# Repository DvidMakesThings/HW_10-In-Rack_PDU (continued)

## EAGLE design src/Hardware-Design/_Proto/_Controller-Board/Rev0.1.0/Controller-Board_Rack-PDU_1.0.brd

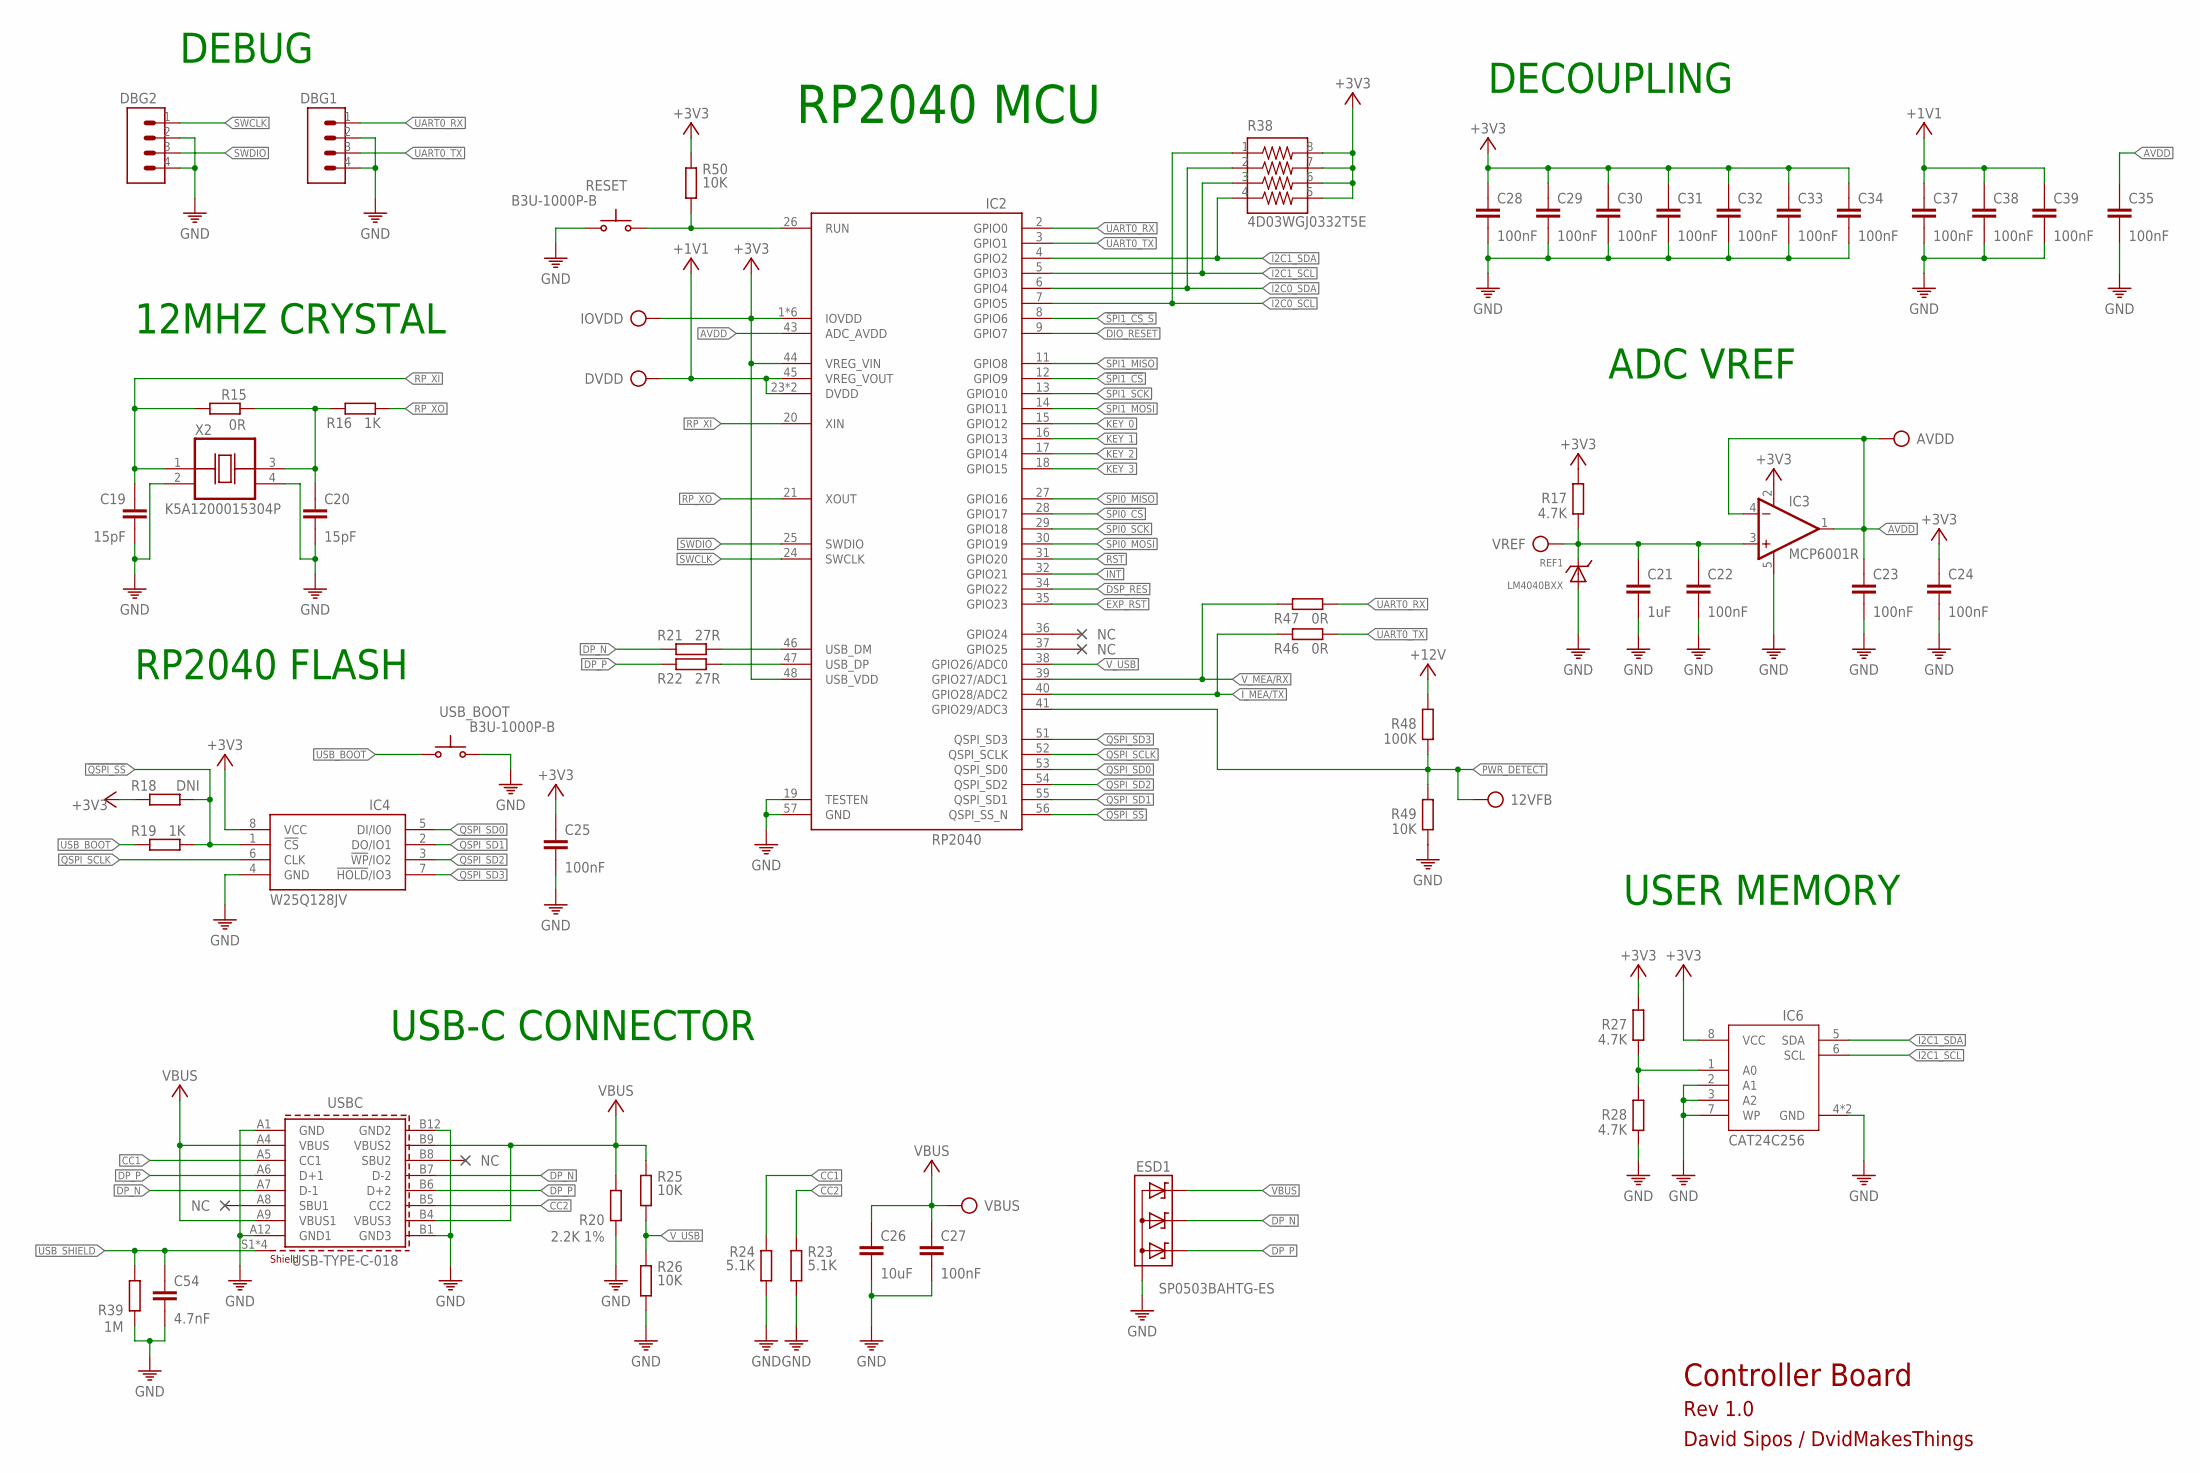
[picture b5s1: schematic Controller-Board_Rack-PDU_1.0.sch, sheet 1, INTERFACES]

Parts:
12VFB: TP
AVDD: TP
C19, C20: 15pF; C0402
C21: 1uF; C0402
C22, C23, C24, C25, C28, C29, C30, C31, C32, C33, C34, C35, C37, C38, C39: 100nF; C0402
C26: 10uF; 0805
C27: 100nF; 0402
C54: 4.7nF; 0402
DBG1, DBG2: CON-1X4; 1X4
DVDD: TP
ESD1: SP0503BAHTG-ES; SOT143
IC2: RP2040; QFN40P700X700X100-57T510
IC3: MCP6001R; SOT23-5
IC4: W25Q128JVPIQ; SON127P600X500X75-8N
IC6: CAT24C256HU4IGT3; SON50P300X200X50-9T130X140N
IOVDD: TP
R15, R46, R47: 0R; 0402
R16, R19: 1K; 0402
R17, R27, R28: 4.7K; 0402
R18: DNI; 0402
R20: 2.2K 1%; 0402
R21, R22: 27R; 0402
R23, R24: 5.1K; 0402
R25, R26, R49, R50: 10K; 0402
R38: 4D03WGJ0332T5E; 742C083103JP
R39: 1M; 0402
R48: 100K; 0402
REF1: LM4040BXX; SOT23
RESET: B3U-1000P-B; SWITCH-OMRON_B3U-1000P
USBC: USB-TYPE-C-018; 629722000214
USB_BOOT: B3U-1000P-B; SWITCH-OMRON_B3U-1000P
VBUS: TP
VREF: TP
X2: K5A1200015304P; OSCCC500X320X130

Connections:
!INT: IC2.32 (GPIO21); also elsewhere on the board
!QSPI_SS: IC2.56 (QSPI_SS_N), IC4.1 (!CS), R18.1, R19.2
!RST: IC2.31 (GPIO20); also elsewhere on the board
!SPI0_CS: IC2.28 (GPIO17); also elsewhere on the board
!SPI1_CS: IC2.12 (GPIO9); also elsewhere on the board
!SPI1_CS_S: IC2.8 (GPIO6); also elsewhere on the board
+1V1: C37.1, C38.1, C39.1, DVDD.TP, IC2.23 (DVDD), IC2.45 (VREG_VOUT), IC2.50 (DVDD)
+3V3: C24.1, C25.1, C28.1, C29.1, C30.1, C31.1, C32.1, C33.1, C34.1, IC2.1 (IOVDD), IC2.10 (IOVDD), IC2.22 (IOVDD), IC2.33 (IOVDD), IC2.42 (IOVDD), IC2.44 (VREG_VIN), IC2.48 (USB_VDD), IC2.49 (IOVDD), IC3.2 (V+), IC4.8 (VCC), IC6.8 (VCC), IOVDD.TP, R17.2, R18.2, R27.2, R38.5, R38.6, R38.7, R38.8, R50.1; also elsewhere on the board
+12V: R48.2; also elsewhere on the board
AVDD: AVDD.TP, C23.1, C35.1, IC2.43 (ADC_AVDD), IC3.1 (OUT), IC3.4 (-IN)
CC1: R24.1, USBC.A5 (CC1)
CC2: R23.1, USBC.B5 (CC2)
DIO_RESET: IC2.9 (GPIO7); also elsewhere on the board
DP_N: ESD1.3 (C2), R21.1, USBC.A7 (D-1), USBC.B7 (D-2)
DP_P: ESD1.2 (C1), R22.1, USBC.A6 (D+1), USBC.B6 (D+2)
DSP_RES: IC2.34 (GPIO22); also elsewhere on the board
EXP_RST: IC2.35 (GPIO23); also elsewhere on the board
GND: C19.2, C20.2, C21.2, C22.2, C23.2, C24.2, C25.2, C26.2, C27.2, C28.2, C29.2, C30.2, C31.2, C32.2, C33.2, C34.2, C35.2, C37.2, C38.2, C39.2, C54.2, DBG1.2, DBG1.4, DBG2.2, DBG2.4, ESD1.1 (A), IC2.19 (TESTEN), IC2.57 (GND), IC3.5 (V-), IC4.4 (GND), IC6.2 (A1), IC6.3 (A2), IC6.4 (GND), IC6.7 (WP), IC6.9 (GND), R20.2, R23.2, R24.2, R26.2, R28.1, R39.2, R49.1, REF1.2 (A), REF1.3 (A), RESET.2 (S), USBC.A1 (GND), USBC.A12 (GND1), USBC.B1 (GND3), USBC.B12 (GND2), USB_BOOT.2 (S), X2.2 (VSS), X2.4 (VDD); also elsewhere on the board
I2C0_SCL: IC2.7 (GPIO5), R38.1; also elsewhere on the board
I2C0_SDA: IC2.6 (GPIO4), R38.2; also elsewhere on the board
I2C1_SCL: IC2.5 (GPIO3), IC6.6 (SCL), R38.3
I2C1_SDA: IC2.4 (GPIO2), IC6.5 (SDA), R38.4
I_MEA/TX: IC2.40 (GPIO28/ADC2), R46.1; also elsewhere on the board
KEY_0: IC2.15 (GPIO12); also elsewhere on the board
KEY_1: IC2.16 (GPIO13); also elsewhere on the board
KEY_2: IC2.17 (GPIO14); also elsewhere on the board
KEY_3: IC2.18 (GPIO15); also elsewhere on the board
unnamed: C20.1, R15.2, R16.1, X2.3 (OUT)
unnamed: IC2.26 (RUN), R50.2, RESET.1
unnamed: IC6.1 (A0), R27.1, R28.2
PWR_DETECT: 12VFB.TP, IC2.41 (GPIO29/ADC3), R48.1, R49.2
QSPI_SCLK: IC2.52 (QSPI_SCLK), IC4.6 (CLK)
QSPI_SD0: IC2.53 (QSPI_SD0), IC4.5 (DI/IO0)
QSPI_SD1: IC2.55 (QSPI_SD1), IC4.2 (DO/IO1)
QSPI_SD2: IC2.54 (QSPI_SD2), IC4.3 (!WP!/IO2)
QSPI_SD3: IC2.51 (QSPI_SD3), IC4.7 (!HOLD!/IO3)
RP_XI: C19.1, IC2.20 (XIN), R15.1, X2.1 (CON)
RP_XO: IC2.21 (XOUT), R16.2
SPI0_MISO: IC2.27 (GPIO16); also elsewhere on the board
SPI0_MOSI: IC2.30 (GPIO19); also elsewhere on the board
SPI0_SCK: IC2.29 (GPIO18); also elsewhere on the board
SPI1_MISO: IC2.11 (GPIO8); also elsewhere on the board
SPI1_MOSI: IC2.14 (GPIO11); also elsewhere on the board
SPI1_SCK: IC2.13 (GPIO10); also elsewhere on the board
SWCLK: DBG2.1, IC2.24 (SWCLK)
SWDIO: DBG2.3, IC2.25 (SWDIO)
UART0_RX: DBG1.1, IC2.2 (GPIO0), R47.2
UART0_TX: DBG1.3, IC2.3 (GPIO1), R46.2
USB_BOOT: R19.1, USB_BOOT.1
USB_DP_N: IC2.46 (USB_DM), R21.2
USB_DP_P: IC2.47 (USB_DP), R22.2
USB_SHIELD: C54.1, R39.1, USBC.S1 (SHIELD), USBC.S2 (SHIELD), USBC.S3 (SHIELD), USBC.S4 (SHIELD)
VBUS: C26.1, C27.1, ESD1.4 (C3), R20.1, R25.1, USBC.A4 (VBUS), USBC.A9 (VBUS1), USBC.B4 (VBUS3), USBC.B9 (VBUS2), VBUS.TP
VREF: C21.1, C22.1, IC3.3 (+IN), R17.1, REF1.1 (C), VREF.TP
V_MEA/RX: IC2.39 (GPIO27/ADC1), R47.1; also elsewhere on the board
V_USB: IC2.38 (GPIO26/ADC0), R25.2, R26.1

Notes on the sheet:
USB-C CONNECTOR
DECOUPLING
12MHZ CRYSTAL
RP2040 MCU
RP2040 FLASH
USER MEMORY
ADC VREF
DEBUG
Controller Board
Rev 1.0
David Sipos / DvidMakesThings

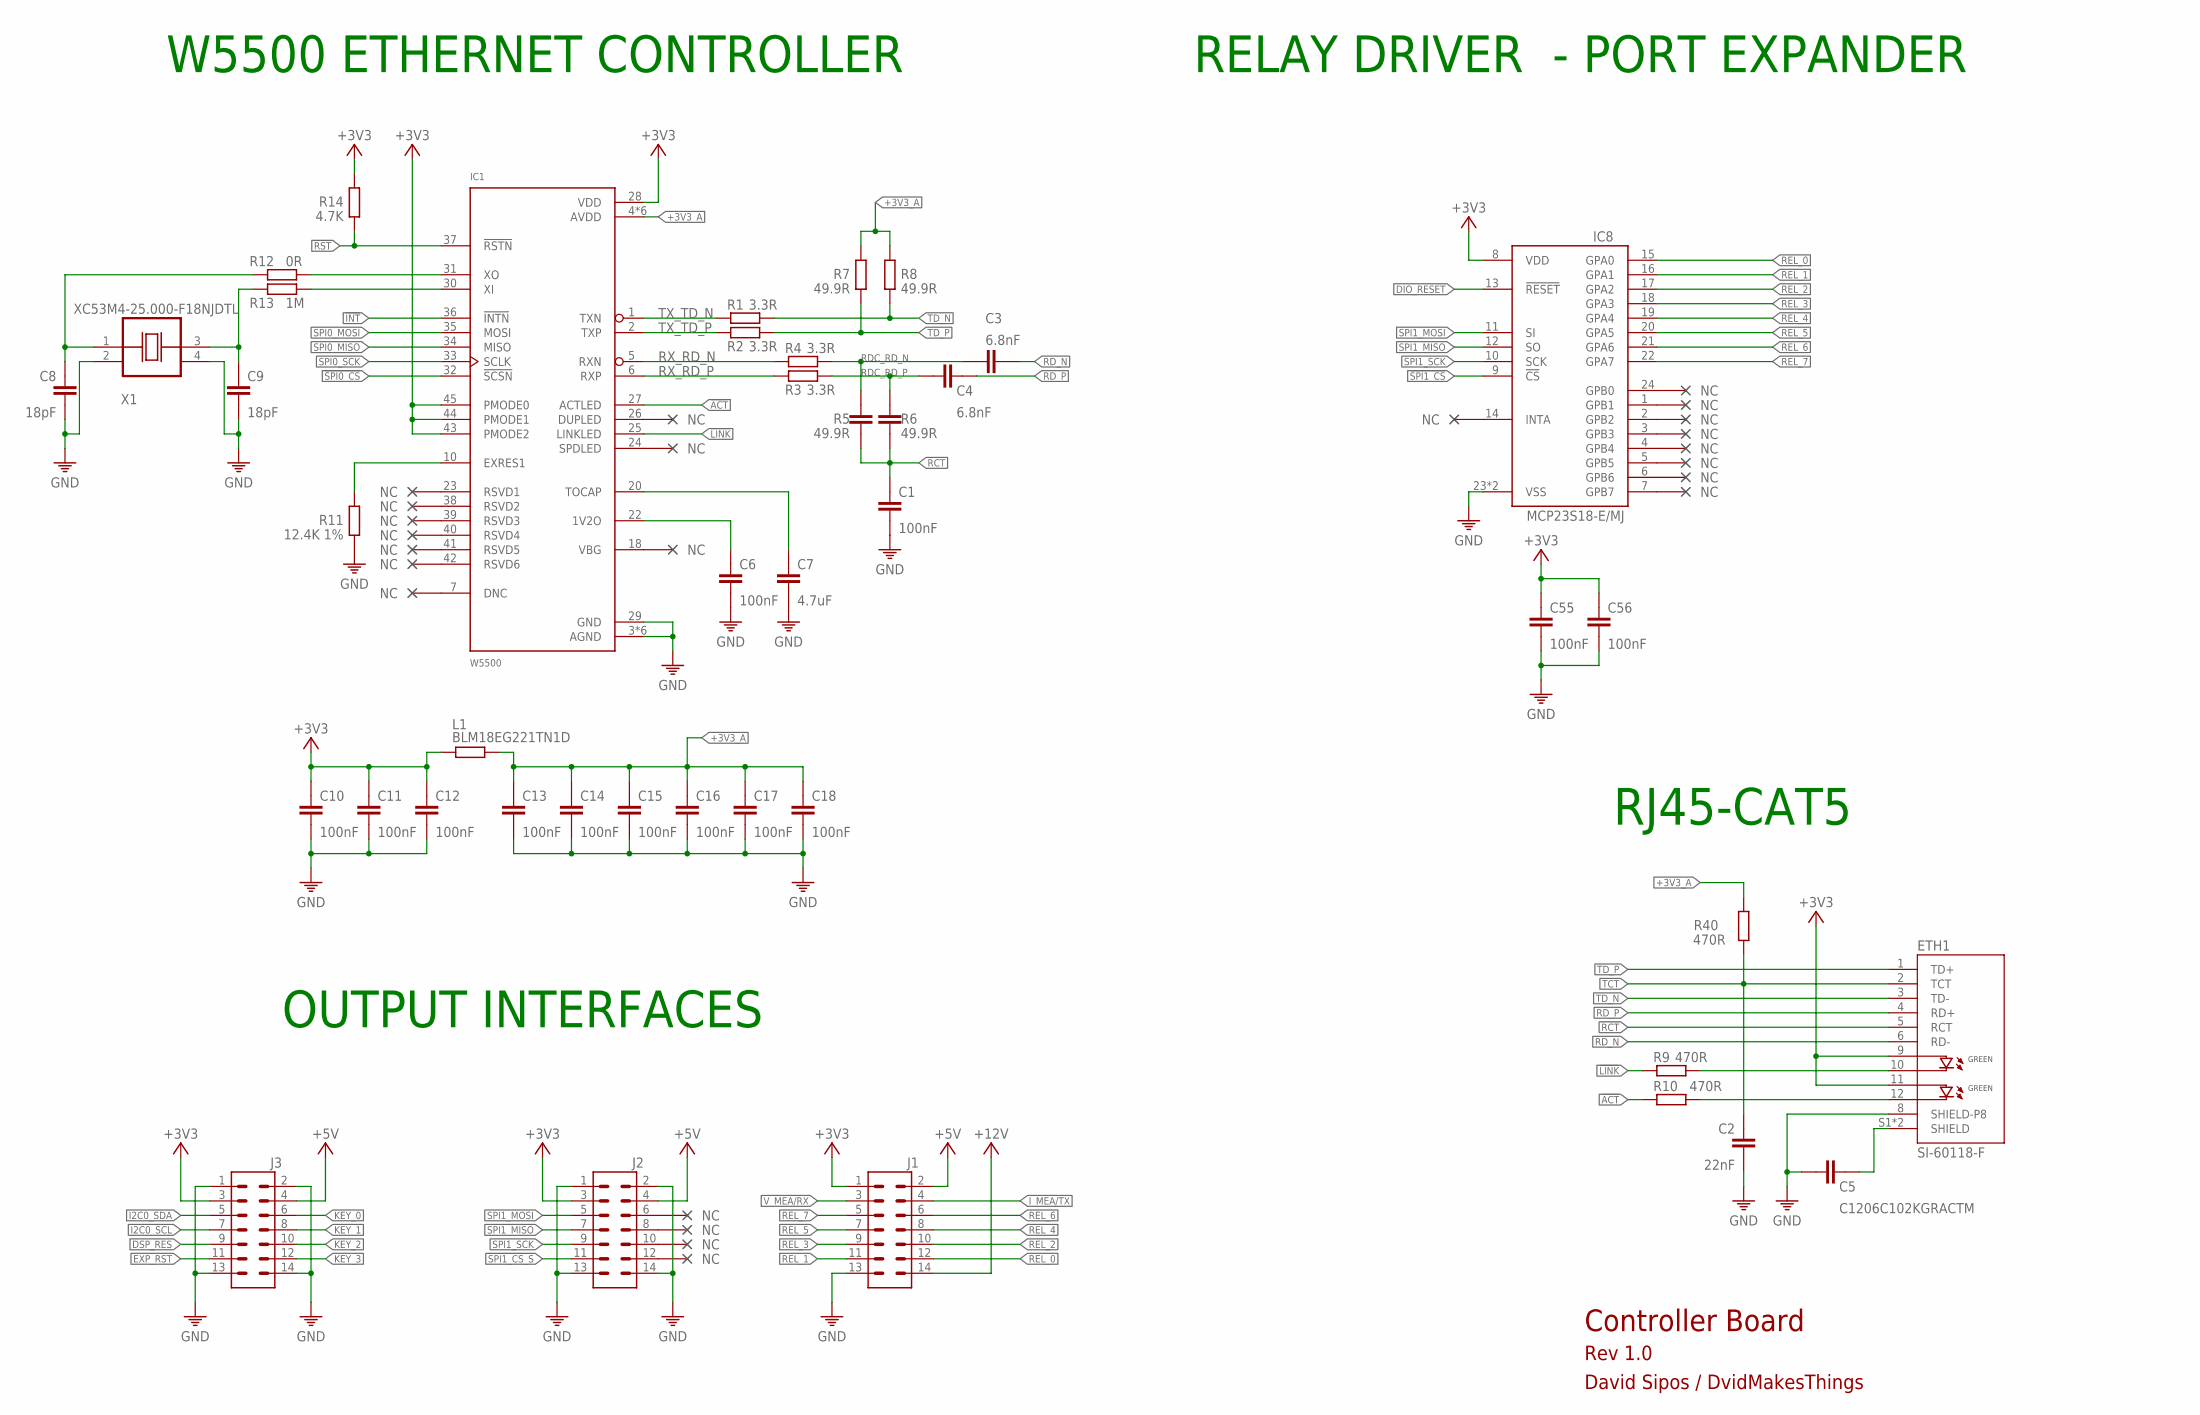
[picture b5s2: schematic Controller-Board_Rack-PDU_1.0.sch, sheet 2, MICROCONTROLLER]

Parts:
C1, C6, C10, C11, C12, C13, C14, C15, C16, C17, C18, C55, C56: 100nF; C0402
C2: 22nF; C0402
C3, C4: 6.8nF; C0402
C5: C1206C102KGRACTM; C1206
C7: 4.7uF; C0402
C8, C9: 18pF; C0402
ETH1: SI-60118-F; RJ45-CAT5
IC1: W5500; LQFP48
IC8: MCP23S18-E/MJ; QFN50P400X400X100-25T265
J1, J2, J3: CON-2X7; 2X7
L1: BLM18EG221TN1D; 0603
R1, R2, R3, R4: 3.3R; 0402
R5, R6: 49.9R; C0402
R7, R8: 49.9R; 0402
R9, R10, R40: 470R; 0402
R11: 12.4K 1%; 0402
R12: 0R; 0402
R13: 1M; 0402
R14: 4.7K; 0402
X1: XC53M4-25.000-F18NJDTL; OSCCC500X320X130

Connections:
!ACT: IC1.27 (ACTLED), R10.1
!INT: IC1.36 (!INTN); also elsewhere on the board
!LINK: IC1.25 (LINKLED), R9.1
!RST: IC1.37 (!RSTN), R14.1; also elsewhere on the board
!SPI0_CS: IC1.32 (!SCSN); also elsewhere on the board
!SPI1_CS: IC8.9 (!CS); also elsewhere on the board
!SPI1_CS_S: J2.11; also elsewhere on the board
+3V3: C10.1, C11.1, C12.1, C55.1, C56.1, ETH1.9 (GA1), ETH1.11 (GA2), IC1.28 (VDD), IC1.43 (PMODE2), IC1.44 (PMODE1), IC1.45 (PMODE0), IC8.8 (VDD), J1.1, J2.3, J3.3, L1.1, R14.2; also elsewhere on the board
+3V3_A: C13.1, C14.1, C15.1, C16.1, C17.1, C18.1, IC1.4 (AVDD), IC1.8 (AVDD), IC1.11 (AVDD), IC1.15 (AVDD), IC1.17 (AVDD), IC1.21 (AVDD), L1.2, R7.2, R8.2, R40.2
+5V: J1.2, J2.4, J3.4; also elsewhere on the board
+12V: J1.14; also elsewhere on the board
CHASSIS: C5.2, ETH1.S1 (SHIELD), ETH1.S2 (SHIELD)
DIO_RESET: IC8.13 (!RESET); also elsewhere on the board
DSP_RES: J3.9; also elsewhere on the board
EXP_RST: J3.11; also elsewhere on the board
GND: C1.2, C2.2, C5.1, C6.2, C7.2, C8.2, C9.2, C10.2, C11.2, C12.2, C13.2, C14.2, C15.2, C16.2, C17.2, C18.2, C55.2, C56.2, ETH1.8 (SHIELD-P8), IC1.3 (AGND), IC1.9 (AGND), IC1.14 (AGND), IC1.16 (AGND), IC1.19 (AGND), IC1.29 (GND), IC1.48 (AGND), IC8.23 (VSS), IC8.25 (VSS), J1.13, J2.1, J2.2, J2.13, J2.14, J3.1, J3.2, J3.13, J3.14, R11.1, X1.2 (VSS), X1.4 (VDD); also elsewhere on the board
I2C0_SCL: J3.7; also elsewhere on the board
I2C0_SDA: J3.5; also elsewhere on the board
I_MEA/TX: J1.4; also elsewhere on the board
KEY_0: J3.6; also elsewhere on the board
KEY_1: J3.8; also elsewhere on the board
KEY_2: J3.10; also elsewhere on the board
KEY_3: J3.12; also elsewhere on the board
unnamed: IC1.10 (EXRES1), R11.2
unnamed: ETH1.10 (GK1), R9.2
unnamed: ETH1.12 (GK2), R10.2
unnamed: C6.1, IC1.22 (1V2O)
unnamed: C7.1, IC1.20 (TOCAP)
unnamed: C8.1, R12.1, X1.1 (CON)
unnamed: C9.1, R13.1, X1.3 (OUT)
unnamed: IC1.31 (XO), R12.2
unnamed: IC1.30 (XI), R13.2
RCT: C1.1, ETH1.5 (RCT), R5.1, R6.1
RDC_RD_N: C3.1, R4.2, R5.2
RDC_RD_P: C4.1, R3.2, R6.2
RD_N: C3.2, ETH1.6 (RD-)
RD_P: C4.2, ETH1.4 (RD+)
REL_0: IC8.15 (GPA0), J1.12
REL_1: IC8.16 (GPA1), J1.11
REL_2: IC8.17 (GPA2), J1.10
REL_3: IC8.18 (GPA3), J1.9
REL_4: IC8.19 (GPA4), J1.8
REL_5: IC8.20 (GPA5), J1.7
REL_6: IC8.21 (GPA6), J1.6
REL_7: IC8.22 (GPA7), J1.5
RX_RD_N: IC1.5 (RXN), R4.1
RX_RD_P: IC1.6 (RXP), R3.1
SPI0_MISO: IC1.34 (MISO); also elsewhere on the board
SPI0_MOSI: IC1.35 (MOSI); also elsewhere on the board
SPI0_SCK: IC1.33 (SCLK); also elsewhere on the board
SPI1_MISO: IC8.12 (SO), J2.7; also elsewhere on the board
SPI1_MOSI: IC8.11 (SI), J2.5; also elsewhere on the board
SPI1_SCK: IC8.10 (SCK), J2.9; also elsewhere on the board
TCT: C2.1, ETH1.2 (TCT), R40.1
TD_N: ETH1.3 (TD-), R1.2, R8.1
TD_P: ETH1.1 (TD+), R2.2, R7.1
TX_TD_N: IC1.1 (TXN), R1.1
TX_TD_P: IC1.2 (TXP), R2.1
V_MEA/RX: J1.3; also elsewhere on the board

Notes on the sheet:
W5500 ETHERNET CONTROLLER
RJ45-CAT5
OUTPUT INTERFACES
RELAY DRIVER - PORT EXPANDER
Controller Board
Rev 1.0
David Sipos / DvidMakesThings

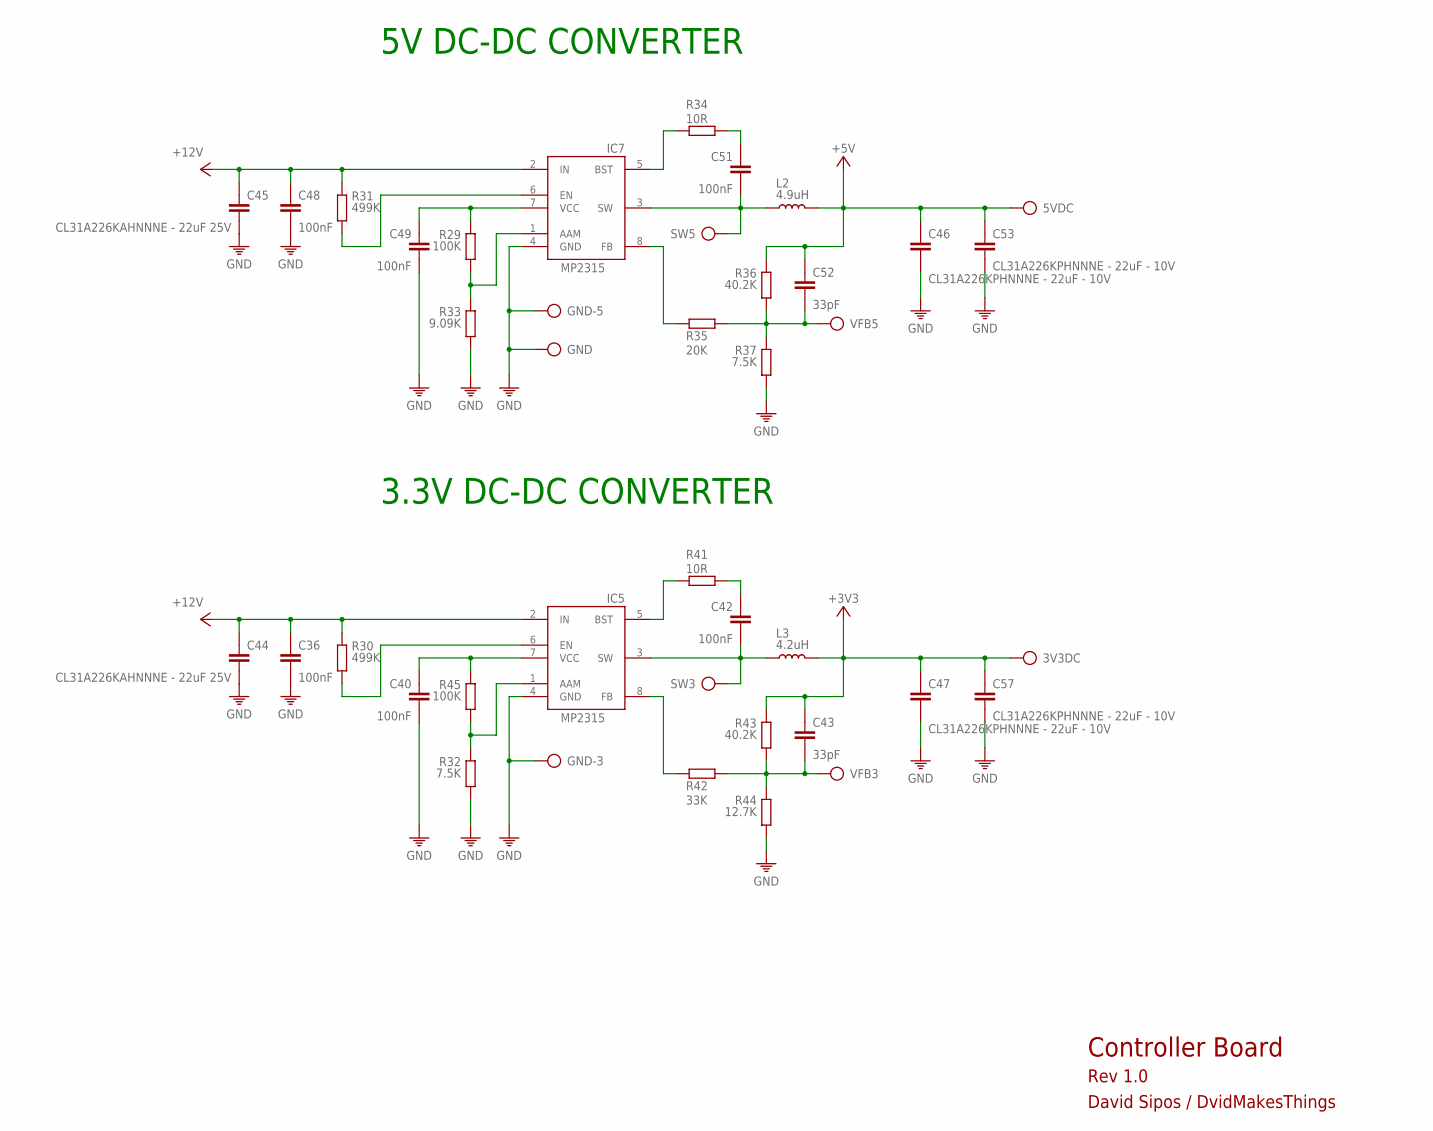
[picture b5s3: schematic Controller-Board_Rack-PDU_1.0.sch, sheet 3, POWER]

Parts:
3V3DC, 5VDC: TP
C36, C40, C42, C48, C49, C51: 100nF; 0402
C43, C52: 33pF; 0402
C44, C45: CL31A226KAHNNNE - 22uF 25V; C1206
C46, C47, C53, C57: CL31A226KPHNNNE - 22uF - 10V; C1206
GND: TP
GND-3, GND-5: TP
IC5: MP2315S; SOT65P280X110-8N
IC7: MP2315GJ-Z; SOT65P280X110-8N
L2: 4.9uH; SRR5228A
L3: 4.2uH; SRR5228A
R29, R45: 100K; 0402
R30, R31: 499K; 0402
R32, R37: 7.5K; 0402
R33: 9.09K; 0402
R34, R41: 10R; 0402
R35: 20K; 0402
R36, R43: 40.2K; 0402
R42: 33K; 0402
R44: 12.7K; 0402
SW3, SW5: TP
VFB3, VFB5: TP

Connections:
+3V3: 3V3DC.TP, C43.1, C47.1, C57.1, L3.2, R43.1; also elsewhere on the board
+5V: 5VDC.TP, C46.1, C52.1, C53.1, L2.2, R36.1; also elsewhere on the board
+12V: C36.1, C44.1, C45.1, C48.1, IC5.2 (IN), IC7.2 (IN), R30.1, R31.1; also elsewhere on the board
GND: C36.2, C40.2, C44.2, C45.2, C46.2, C47.2, C48.2, C49.2, C53.2, C57.2, GND.TP, GND-3.TP, GND-5.TP, IC5.4 (GND), IC7.4 (GND), R32.2, R33.2, R37.2, R44.2; also elsewhere on the board
unnamed: IC5.5 (BST), R41.2
unnamed: IC5.1 (AAM), R32.1, R45.2
unnamed: IC7.1 (AAM), R29.2, R33.1
unnamed: IC7.6 (EN), R31.2
unnamed: C49.1, IC7.7 (VCC), R29.1
unnamed: IC5.8 (FB), R42.1
unnamed: C42.2, IC5.3 (SW), L3.1, SW3.TP
unnamed: C42.1, R41.1
unnamed: C43.2, R42.2, R43.2, R44.1, VFB3.TP
unnamed: IC5.6 (EN), R30.2
unnamed: C40.1, IC5.7 (VCC), R45.1
unnamed: IC7.5 (BST), R34.2
unnamed: IC7.8 (FB), R35.1
unnamed: C51.2, IC7.3 (SW), L2.1, SW5.TP
unnamed: C51.1, R34.1
unnamed: C52.2, R35.2, R36.2, R37.1, VFB5.TP

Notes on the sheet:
5V DC-DC CONVERTER
Controller Board
Rev 1.0
David Sipos / DvidMakesThings
3.3V DC-DC CONVERTER

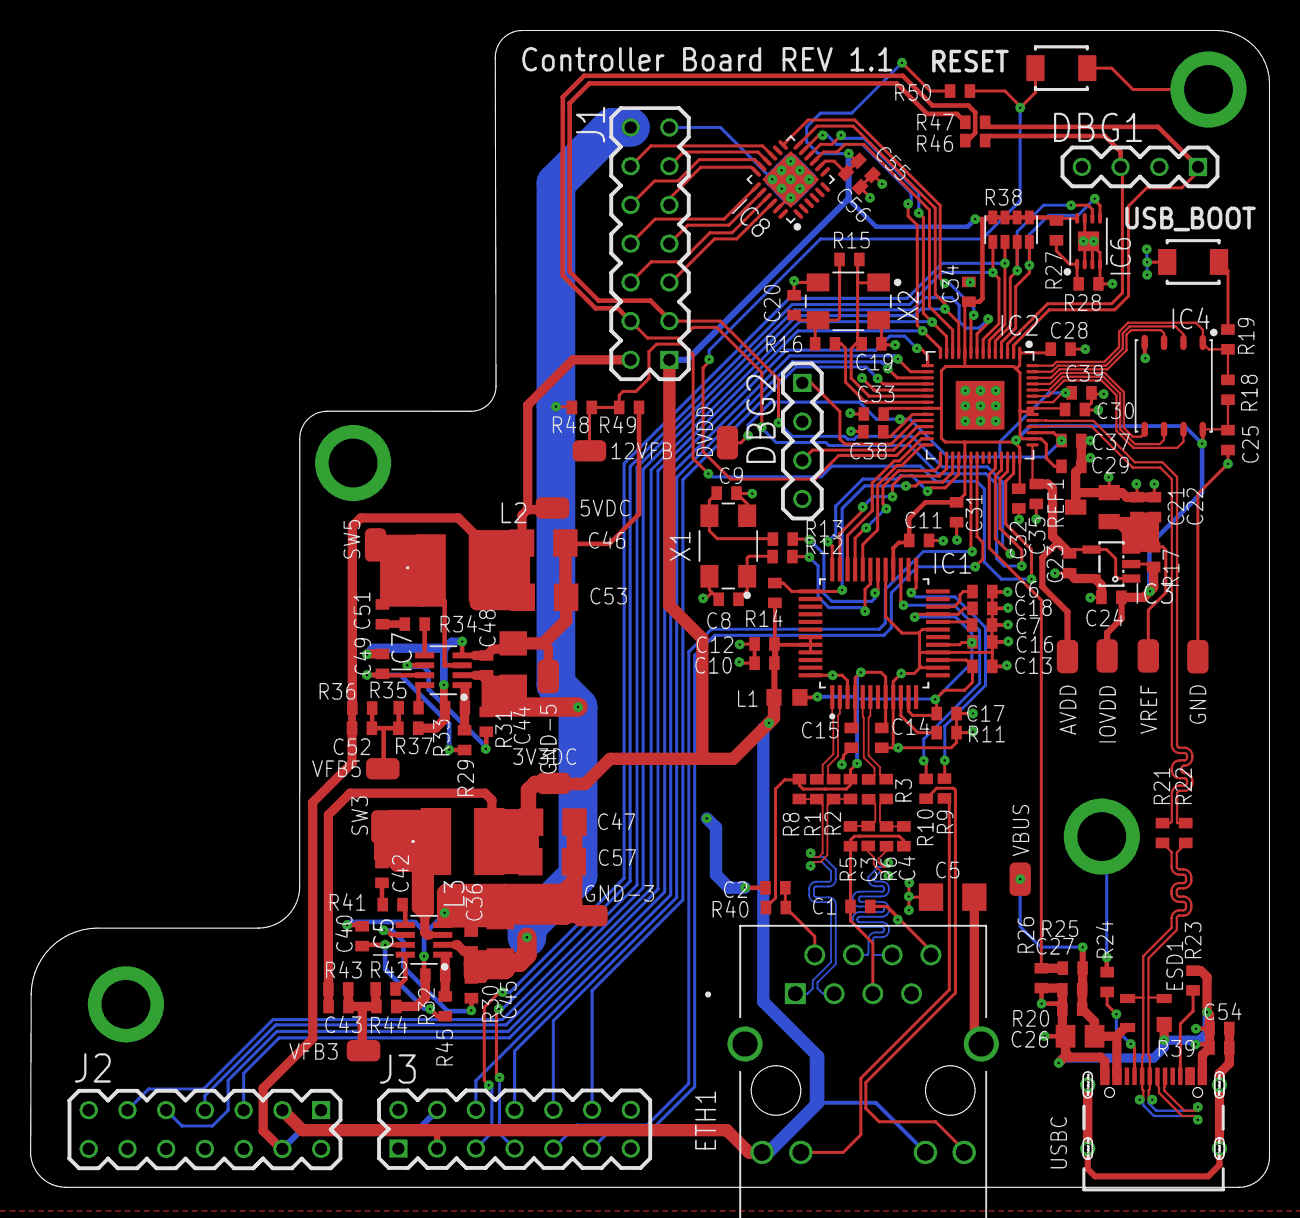
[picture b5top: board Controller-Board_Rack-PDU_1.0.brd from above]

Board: 4 copper layers, 81.3 x 75.9 mm, 144 parts (0 on the bottom side), 106 nets.

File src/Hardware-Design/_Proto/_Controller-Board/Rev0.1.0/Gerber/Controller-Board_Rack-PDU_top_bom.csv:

Comment,Designator,Footprint,LCSC Part #
0R,R12 R15 R46 R47,0402,
1K,R16 R19,0402,
1M,R13 R39,0402,
1uF,C21,C0402,
2.2K 1%,R20,0402,
3.3R,R1 R2 R3 R4,0402,
4.2uH,L3,SRR5228A,
4.7K,R14 R17 R27 R28 R48 R49,0402,
4.7nF,C54,0402,
4.7uF,C7,C0402,
4.9uH,L2,SRR5228A,
4D03WGJ0332T5E,R38,742C083103JP,
5.1K,R23 R24,0402,
5.6K,R25,0402,
6.8nF,C3 C4,C0402,
7.5K,R32 R37,0402,
9.09K,R33,0402,
10K,R26 R50,0402,
10R,R34 R41,0402,
10uF,C26,0805,
12.4K 1%,R11,0402,
12.7K,R44,0402,
15pF,C19 C20,C0402,
18pF,C8 C9,C0402,
20K,R35,0402,
22nF,C2,C0402,
27R,R21 R22,0402,
33K,R42,0402,
33pF,C43 C52,0402,
40.2K,R36 R43,0402,
49.9R,R5 R6,C0402,
49.9R,R7 R8,0402,
100K,R29 R45,0402,
100nF,C1 C6 C10 C11 C12 C13 C14 C15 C16 C17 C18 C22 C23 C24 C25,C0402,
100nF,C27,0402,
100nF,C28 C29 C30 C31 C32 C33 C34 C35,C0402,
100nF,C36,0402,
100nF,C37 C38 C39,C0402,
100nF,C40 C42 C48 C49 C51,0402,
100nF,C55 C56,C0402,
470R,R9 R10 R40,0402,
499K,R30 R31,0402,
B3U-1000P-B,RESET USB_BOOT,SWITCH-OMRON_B3U-1000P,
BLM18EG221TN1D,L1,0603,
C1206C102KGRACTM,C5,C1206,
CAT24C256WI-GT3,IC6,SON50P300X200X50-9T130X140N,
CL31A226KAHNNNE - 22uF 25V,C44 C45,C1206,
CL31A226KPHNNNE - 22uF - 10V,C46 C47 C53 C57,C1206,
DNI,R18,0402,
LM4040BXX,REF1,SOT23,
MCP23S18-E/MJ,IC8,QFN50P400X400X100-25T265,
MCP6001AIDBVRG,IC3,SOT23-5,
MP2315GJ-Z,IC7,SOT65P280X110-8N,
MP2315S ,IC5,SOT65P280X110-8N,
RL250001791,X1,OSCCC500X320X130,
RP2040,IC2,QFN40P700X700X100-57T510,
SP0503BAHTG-ES,ESD1,SOT143,
SX3M12.000B10F20TNN,X2,OSCCC500X320X130,
TP,3V3DC 5VDC 12VFB AVDD DVDD GND GND-3 GND-5 IOVDD SW3 SW5 VBUS VFB3 VFB5 VREF,TP,
USB-TYPE-C-018,USBC,629722000214,
W25Q128JVPIQ,IC4,SON127P600X500X75-8N,
W5500,IC1,LQFP48,

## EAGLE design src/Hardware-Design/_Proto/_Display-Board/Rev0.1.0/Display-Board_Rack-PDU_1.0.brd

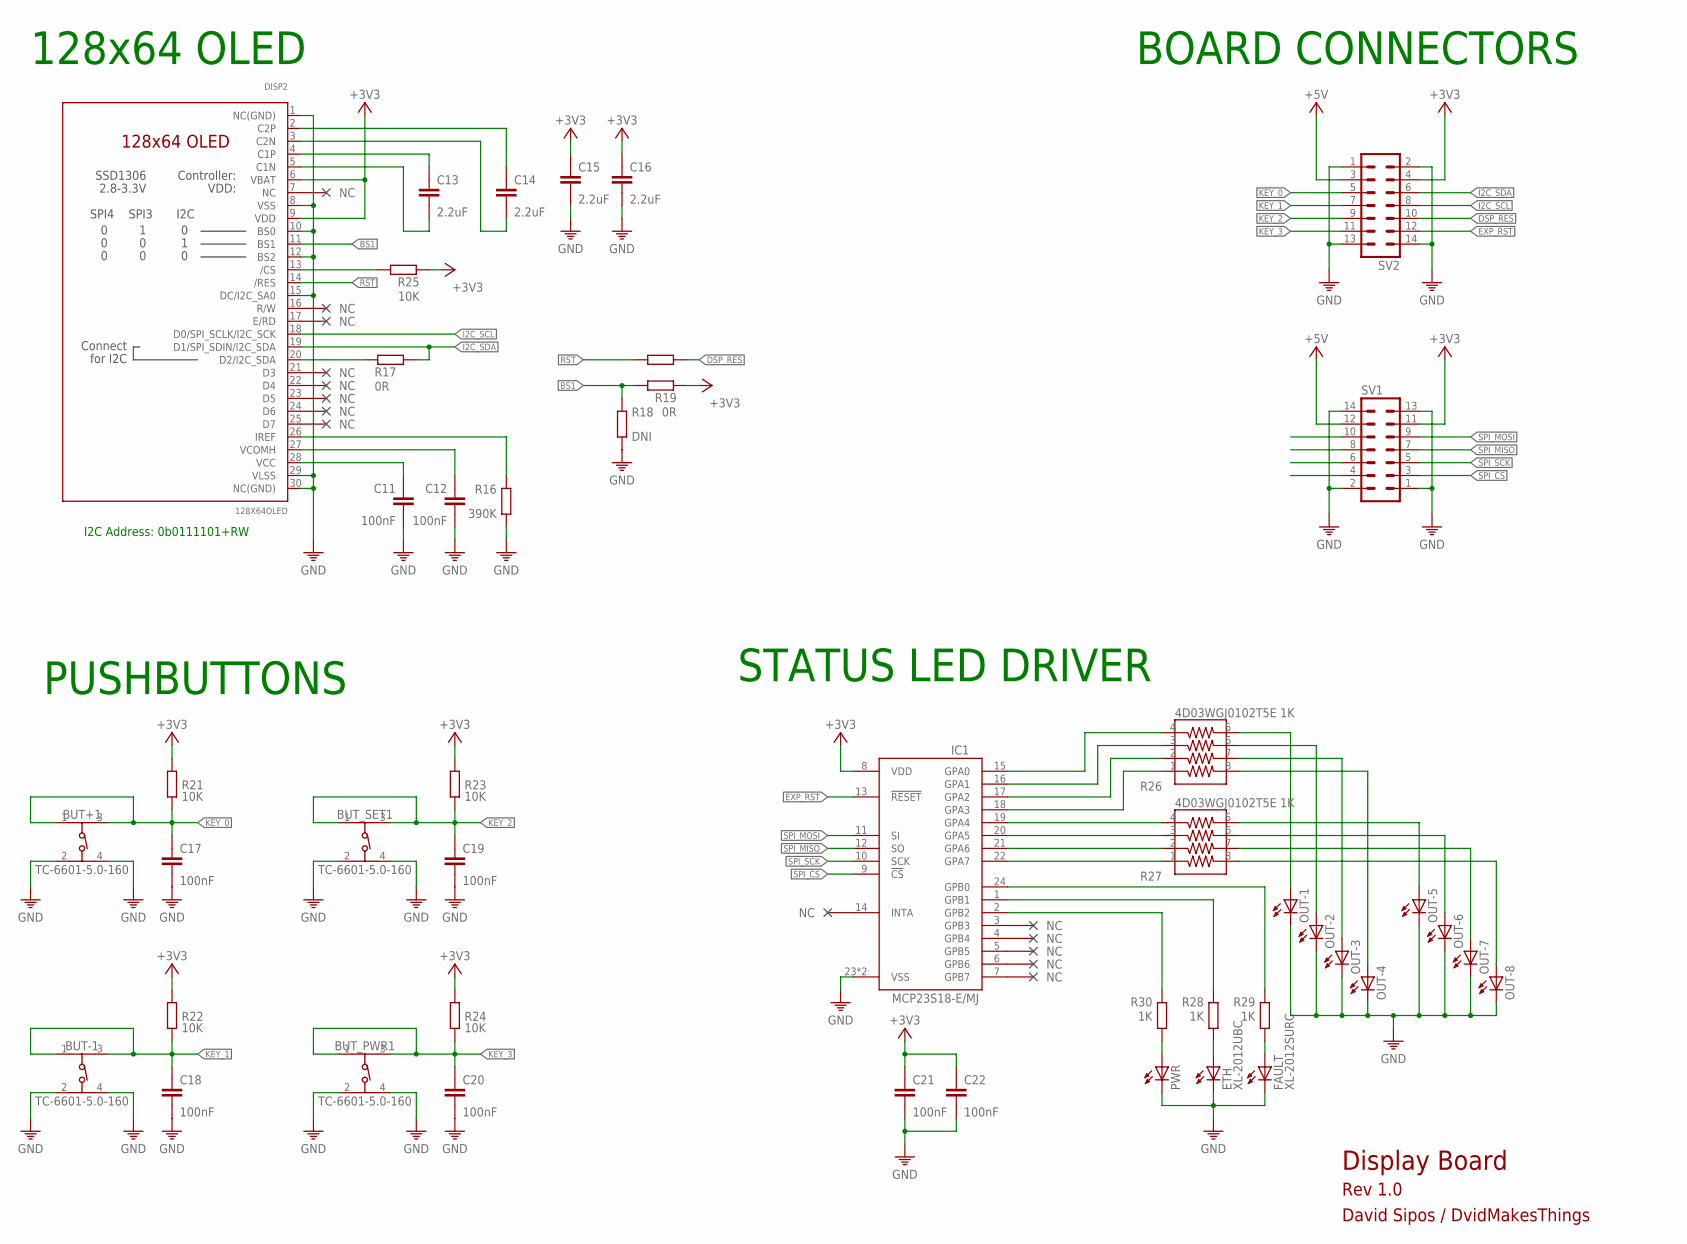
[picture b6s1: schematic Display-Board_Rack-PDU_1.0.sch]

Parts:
BUT+1: TC-6601-5.0-160; 430182043816
BUT-1: TC-6601-5.0-160; 430182043816
BUT_PWR1: TC-6601-5.0-160; 430182043816
BUT_SET1: TC-6601-5.0-160; 430182043816
C11, C12, C17, C18, C19, C20, C21, C22: 100nF; 0402
C13, C14, C15, C16: 2.2uF; 0402
DISP2: 128X64OLED; UG2864
ETH: XL-2012UBC; CHIP-LED0805
FAULT: XL-2012SURC; CHIP-LED0805
IC1: MCP23S18-E/MJ; QFN50P400X400X100-25T265
OUT-1, OUT-2, OUT-3, OUT-4, OUT-5, OUT-6, OUT-7, OUT-8: LEDCHIP-LED0805; CHIP-LED0805
PWR: LEDCHIP-LED0805; CHIP-LED0805
R16: 390K; 0402
R17, R19, R20: 0R; 0402
R18: DNI; 0402
R21, R22, R23, R24, R25: 10K; 0402
R26, R27: 4D03WGJ0102T5E 1K; 742C083103JP
R28, R29, R30: 1K; 0402
SV1, SV2: MA07-2W

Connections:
+3V3: C15.1, C16.1, C21.1, C22.1, DISP2.6 (VBAT), DISP2.9 (VDD), IC1.8 (VDD), R19.1, R21.1, R22.1, R23.1, R24.1, R25.1, SV1.11, SV2.4
+5V: SV1.12, SV2.3
BS1: DISP2.11 (BS1), R18.1, R19.2
DSP_RES: R20.2, SV2.10
EXP_RST: IC1.13 (!RESET), SV2.12
GND: BUT+1.2, BUT+1.4, BUT-1.2, BUT-1.4, BUT_PWR1.2, BUT_PWR1.4, BUT_SET1.2, BUT_SET1.4, C11.2, C12.2, C15.2, C16.2, C17.2, C18.2, C19.2, C20.2, C21.2, C22.2, DISP2.1 (NC(GND)), DISP2.8 (VSS), DISP2.10 (BS0), DISP2.12 (BS2), DISP2.15 (DC/I2C_SA0), DISP2.29 (VLSS), DISP2.30 (NC(GND)), ETH.C, FAULT.C, IC1.23 (VSS), IC1.25 (VSS), OUT-1.C, OUT-2.C, OUT-3.C, OUT-4.C, OUT-5.C, OUT-6.C, OUT-7.C, OUT-8.C, PWR.C, R16.2, R18.2, SV1.1, SV1.2, SV1.13, SV1.14, SV2.1, SV2.2, SV2.13, SV2.14
I2C_SCL: DISP2.18 (D0/SPI_SCLK/I2C_SCK), SV2.8
I2C_SDA: DISP2.19 (D1/SPI_SDIN/I2C_SDA), R17.2, SV2.6
KEY_0: BUT+1.1, BUT+1.3, C17.1, R21.2, SV2.5
KEY_1: BUT-1.1, BUT-1.3, C18.1, R22.2, SV2.7
KEY_2: BUT_SET1.1, BUT_SET1.3, C19.1, R23.2, SV2.9
KEY_3: BUT_PWR1.1, BUT_PWR1.3, C20.1, R24.2, SV2.11
unnamed: C13.2, DISP2.5 (C1N)
unnamed: C13.1, DISP2.4 (C1P)
unnamed: C14.2, DISP2.3 (C2N)
unnamed: C14.1, DISP2.2 (C2P)
unnamed: DISP2.26 (IREF), R16.1
unnamed: C11.1, DISP2.28 (VCC)
unnamed: C12.1, DISP2.27 (VCOMH)
unnamed: DISP2.20 (D2/I2C_SDA), R17.1
unnamed: IC1.1 (GPB1), R28.1
unnamed: IC1.2 (GPB2), R30.1
unnamed: IC1.24 (GPB0), R29.1
unnamed: DISP2.13 (/CS), R25.2
unnamed: IC1.15 (GPA0), R26.4
unnamed: IC1.16 (GPA1), R26.3
unnamed: IC1.17 (GPA2), R26.2
unnamed: IC1.18 (GPA3), R26.1
unnamed: IC1.19 (GPA4), R27.4
unnamed: IC1.20 (GPA5), R27.3
unnamed: IC1.21 (GPA6), R27.2
unnamed: IC1.22 (GPA7), R27.1
unnamed: OUT-1.A, R26.5
unnamed: OUT-2.A, R26.6
unnamed: OUT-3.A, R26.7
unnamed: OUT-4.A, R26.8
unnamed: OUT-5.A, R27.5
unnamed: OUT-6.A, R27.6
unnamed: OUT-7.A, R27.7
unnamed: OUT-8.A, R27.8
unnamed: FAULT.A, R29.2
unnamed: ETH.A, R28.2
unnamed: PWR.A, R30.2
RST: DISP2.14 (/RES), R20.1
SPI_CS: IC1.9 (!CS), SV1.3
SPI_MISO: IC1.12 (SO), SV1.7
SPI_MOSI: IC1.11 (SI), SV1.9
SPI_SCK: IC1.10 (SCK), SV1.5

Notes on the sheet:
I2C Address: 0b0111101+RW
BOARD CONNECTORS
128x64 OLED
PUSHBUTTONS
STATUS LED DRIVER
Display Board
Rev 1.0
David Sipos / DvidMakesThings

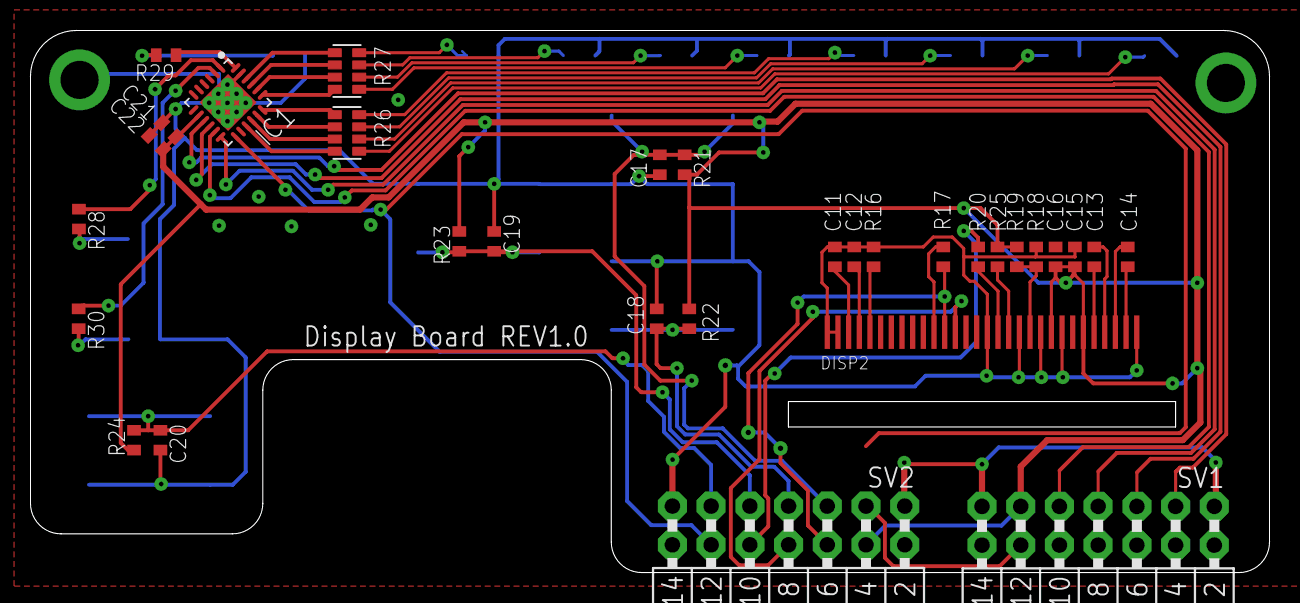
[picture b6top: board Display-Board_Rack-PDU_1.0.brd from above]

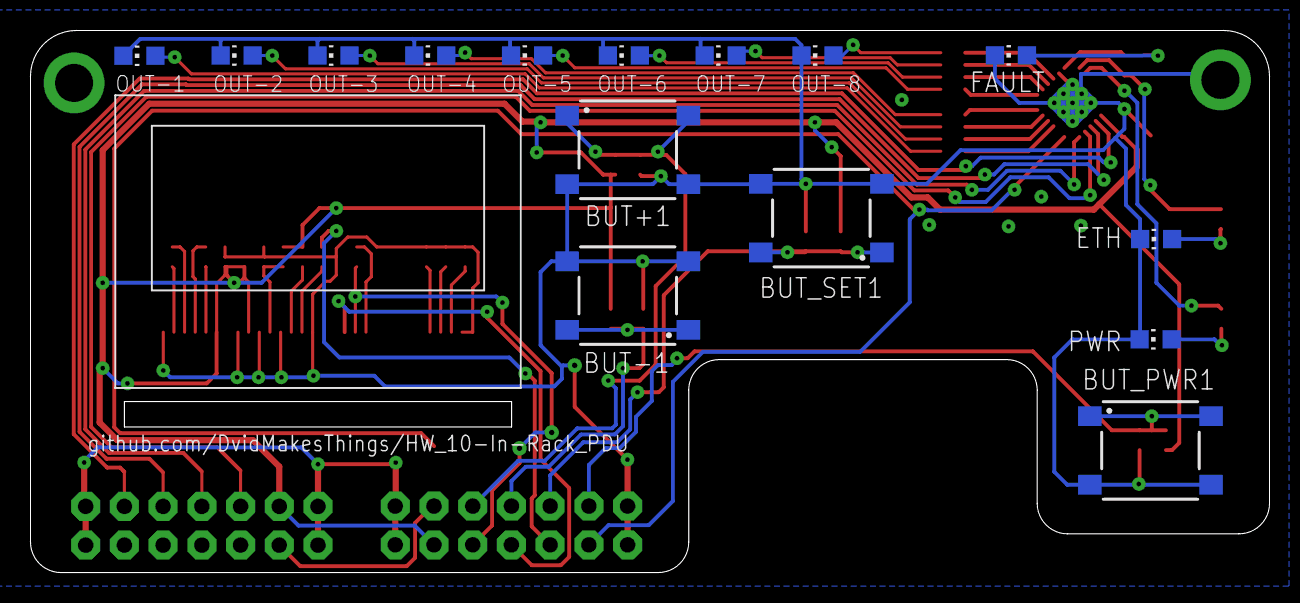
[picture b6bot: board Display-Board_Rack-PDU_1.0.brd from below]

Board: 2 copper layers, 81.3 x 35.6 mm, 46 parts (16 on the bottom side), 48 nets.

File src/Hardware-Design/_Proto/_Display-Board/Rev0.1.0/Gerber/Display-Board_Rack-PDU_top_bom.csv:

Comment,Designator,Footprint,LCSC Part #
,CON3 CON4,2X7-SIDE,
0R,R17 R19 R20,0402,
1K,R28 R29 R30,0402,
2.2uF,C13 C14 C15 C16,0402,
4D03WGJ0102T5E 1K,R26 R27,742C083103JP,
10K,R21 R22 R23 R24 R25,0402,
100nF,C11 C12 C17 C18 C19 C20 C21 C22,0402,
128X64OLED,DISP2,UG2864,
390K,R16,0402,
DNI,R18,0402,
MCP23S18-E/MJ,IC1,QFN50P400X400X100-25T265,
,CON3 CON4,2X7-SIDE,
,OUT-1 OUT-2 OUT-3 OUT-4 OUT-5 OUT-6 OUT-7 OUT-8 PWR,CHIP-LED0805,
TC-6601-5.0-160,BUT+1 BUT-1 BUT_PWR1 BUT_SET1,4.30182E+11,
XL-2012SURC,FAULT,CHIP-LED0805,
XL-2012UBC,ETH,CHIP-LED0805,
